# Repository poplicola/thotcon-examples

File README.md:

# Touch Wheel Badge - Demo Firmware Collection

This repository contains cleaned-up demo firmware for the touch wheel badge, suitable for public release and custom projects. Three different firmware examples are provided to showcase various capabilities of the hardware.

## Repository Contents

### 1. `tonechaser/` - Musical Tone Explorer
Advanced musical demonstration with multiple modes:
- **Free Play Mode**: Continuous tone generation based on touch position
- **Scale Mode**: Quantized musical scales
- **Chord Mode**: Play musical chords
- **Arpeggio Mode**: Automatic arpeggios
- **Visual Wheel**: Colorful wheel visualization with effects
- **Musical Features**: Multiple scales (Major, Minor, Pentatonic, Blues)

### 2. `working/` - Basic Touch Wheel Test
Simple touch wheel demonstration:
- **Touch Detection**: Basic capacitive touch wheel functionality
- **LED Indicators**: 6 LEDs that light up based on touch position
- **Calibration**: Automatic baseline calibration
- **Serial Output**: Debug data for development
- **Visual Feedback**: Simple wheel visualization on display

### 3. `wheel_visualization/` - Full Interactive Demo
Additional badge firmware with menu system:
- **Touch Wheel Demo**: Interactive capacitive touch wheel with visual feedback
- **Menu System**: Navigate between different modes using the touch wheel
- **Audio Feedback**: Simple tone feedback for interactions
- **Mini Games**: Placeholder for future game implementations
- **Credits Screen**: Information about the original creators
- **Clean Architecture**: Modular code structure for easy customization

## Hardware Requirements

All firmware examples work with the same hardware:

- **ESP32 microcontroller** (ESP32 Thing or compatible)
- **ST7789 TFT Display** (240x320 pixels)
- **6 LEDs** connected to GPIO pins
- **3 Capacitive touch sensors** for wheel input
- **Buzzer** for audio feedback
- **Center button** (capacitive touch)

## Pin Configuration

### TFT Display Pins
```cpp
#define TFT_MISO 19
#define TFT_MOSI 23
#define TFT_SCLK 18
#define TFT_CS   15  // Chip select control pin
#define TFT_DC    2  // Data Command control pin
#define TFT_RST   4  // Reset pin
```

### LED Pins
```cpp
#define LED_1_PIN 21
#define LED_2_PIN 22
#define LED_3_PIN 19
#define LED_4_PIN 17
#define LED_5_PIN 16
#define LED_6_PIN 25
```

### Touch Sensor Pins
```cpp
#define SELECT_PIN 27  // Center button
#define Q1_PIN 13      // Touch sensor 1
#define Q2_PIN 12      // Touch sensor 2
#define Q3_PIN 14      // Touch sensor 3
```

### Audio Pin
```cpp
#define BUZZER_PIN 5
```

## Getting Started

### 1. Install Arduino IDE
Download and install the [Arduino IDE](https://www.arduino.cc/en/software) if you haven't already.

### 2. Install ESP32 Board Package
1. In Arduino IDE, go to **File > Preferences**
2. Add this URL to "Additional Board Manager URLs":
   ```
   https://espressif.github.io/arduino-esp32/package_esp32_index.json
   ```
3. Go to **Tools > Board > Boards Manager**
4. Search for "esp32" and install the ESP32 package by Espressif

### 3. Install Required Libraries

#### TFT_eSPI Library
1. Go to **Sketch > Include Library > Manage Libraries**
2. Search for "TFT_eSPI" and install the library by Bodmer
3. **IMPORTANT**: You must configure the library for the ST7789 display

#### Configure TFT_eSPI for ST7789
1. Navigate to your Arduino libraries folder:
   - **Windows**: `Documents/Arduino/libraries/TFT_eSPI/`
   - **Mac**: `~/Documents/Arduino/libraries/TFT_eSPI/`
   - **Linux**: `~/Arduino/libraries/TFT_eSPI/`

2. Open `User_Setup.h` in a text editor

3. Comment out any existing driver and add these lines:
   ```cpp
   #define ST7789_DRIVER    // Configure for ST7789 display
   
   // Pin definitions (add these to User_Setup.h)
   #define TFT_MISO 19
   #define TFT_MOSI 23
   #define TFT_SCLK 18
   #define TFT_CS   15
   #define TFT_DC    2
   #define TFT_RST   4
   
   #define TFT_WIDTH  240
   #define TFT_HEIGHT 320
   ```

### 4. Choose and Upload Firmware
1. Choose one of the three firmware options:
   - `tonechaser/tonechaser.ino` - Musical demonstration
   - `working/working.ino` - Basic touch wheel test
   - `wheel_visualization/wheel_visualization.ino` - Full interactive demo
2. Open the chosen `.ino` file in Arduino IDE
3. Select your ESP32 board: **Tools > Board > ESP32 Arduino > ESP32 Thing** (or your specific ESP32 variant)
4. Select the correct COM port: **Tools > Port**
5. Click **Upload**

## Firmware Comparison

| Feature | working | tonechaser | wheel_visualization |
|---------|---------|------------|-------------------|
| Touch Detection | ✅ Basic | ✅ Advanced | ✅ Advanced |
| LED Control | ✅ | ✅ | ✅ |
| Audio Feedback | ❌ | ✅ Musical | ✅ Simple |
| Visual Display | ✅ Simple | ✅ Colorful | ✅ Interactive |
| Menu System | ❌ | ❌ | ✅ |
| Multiple Modes | ❌ | ✅ | ✅ |
| Calibration | ✅ | ✅ | ✅ |
| Serial Debug | ✅ | ❌ | ✅ |
| Code Complexity | Simple | Medium | Advanced |

## Usage

### Controls (All Firmware)
- **Touch Wheel**: Touch around the capacitive wheel to see visual feedback and light up LEDs
- **Center Button**: Press the center capacitive button (varies by firmware)
- **Calibration**: All firmware automatically calibrates on startup (don't touch during this phase)

### Specific Features by Firmware

#### `working/` - Basic Test
- Simple touch detection with LED feedback
- Displays raw sensor values and touch angle
- Best for hardware testing and development

#### `tonechaser/` - Musical Explorer
- Multiple musical modes (Free Play, Scale, Chord, Arpeggio)
- Press center button to cycle through modes
- Rich visual effects and musical scales
- Continuous tone generation based on touch position

#### `wheel_visualization/` - Interactive Demo
- Full menu system with navigation
- Touch wheel demo mode
- Placeholder mini-games section
- Credits screen
- Most complete user experience

## Customization

All firmware examples are designed to be easily modified:

- **Pin Configuration**: Modify pin definitions in each sketch
- **Touch Sensitivity**: Adjust touch thresholds
- **Colors and Effects**: Customize visual appearance
- **Audio**: Modify tones and musical scales
- **Menu Items**: Add new screens and functionality

## Troubleshooting

### Display Issues
- **Blank Screen**: Check TFT_eSPI configuration in `User_Setup.h`
- **Wrong Colors**: Verify `ST7789_DRIVER` is defined
- **Upside Down**: Adjust `tft.setRotation(0)` in setup()

### Touch Issues
- **No Touch Response**: Check capacitive touch sensor connections
- **Erratic Behavior**: May need recalibration or threshold adjustment
- **LEDs Not Working**: Verify LED pin connections

### Compilation Errors
- **Library Not Found**: Install TFT_eSPI library via Library Manager
- **Pin Conflicts**: Check pin definitions match your hardware setup
- **Memory Issues**: Try a simpler firmware if running out of memory

## Hardware Notes

This firmware was originally designed for a specific touch wheel badge but can be adapted for custom hardware. The touch wheel uses three capacitive sensors positioned 120° apart to triangulate touch position around a circular perimeter.

The algorithms calculate touch position using trigonometric interpolation between the three sensor readings, providing smooth and accurate position detection around the full 360° wheel.

## Development

Each firmware demonstrates different aspects of the hardware capabilities:

- **`working/`**: Foundation for understanding the basic touch detection algorithms
- **`tonechaser/`**: Advanced audio synthesis and visual effects
- **`wheel_visualization/`**: Complete UI framework and menu system

Use these as starting points for your own projects or as learning examples for capacitive touch wheel implementations.

## Credits

All credit to **Fourfold**. Visit [fourfold.co](https://fourfold.co) for more info.

## License

This is demonstration firmware provided as-is for educational and development purposes. WiFi functionality, splash screens, and proprietary content have been removed for public release.

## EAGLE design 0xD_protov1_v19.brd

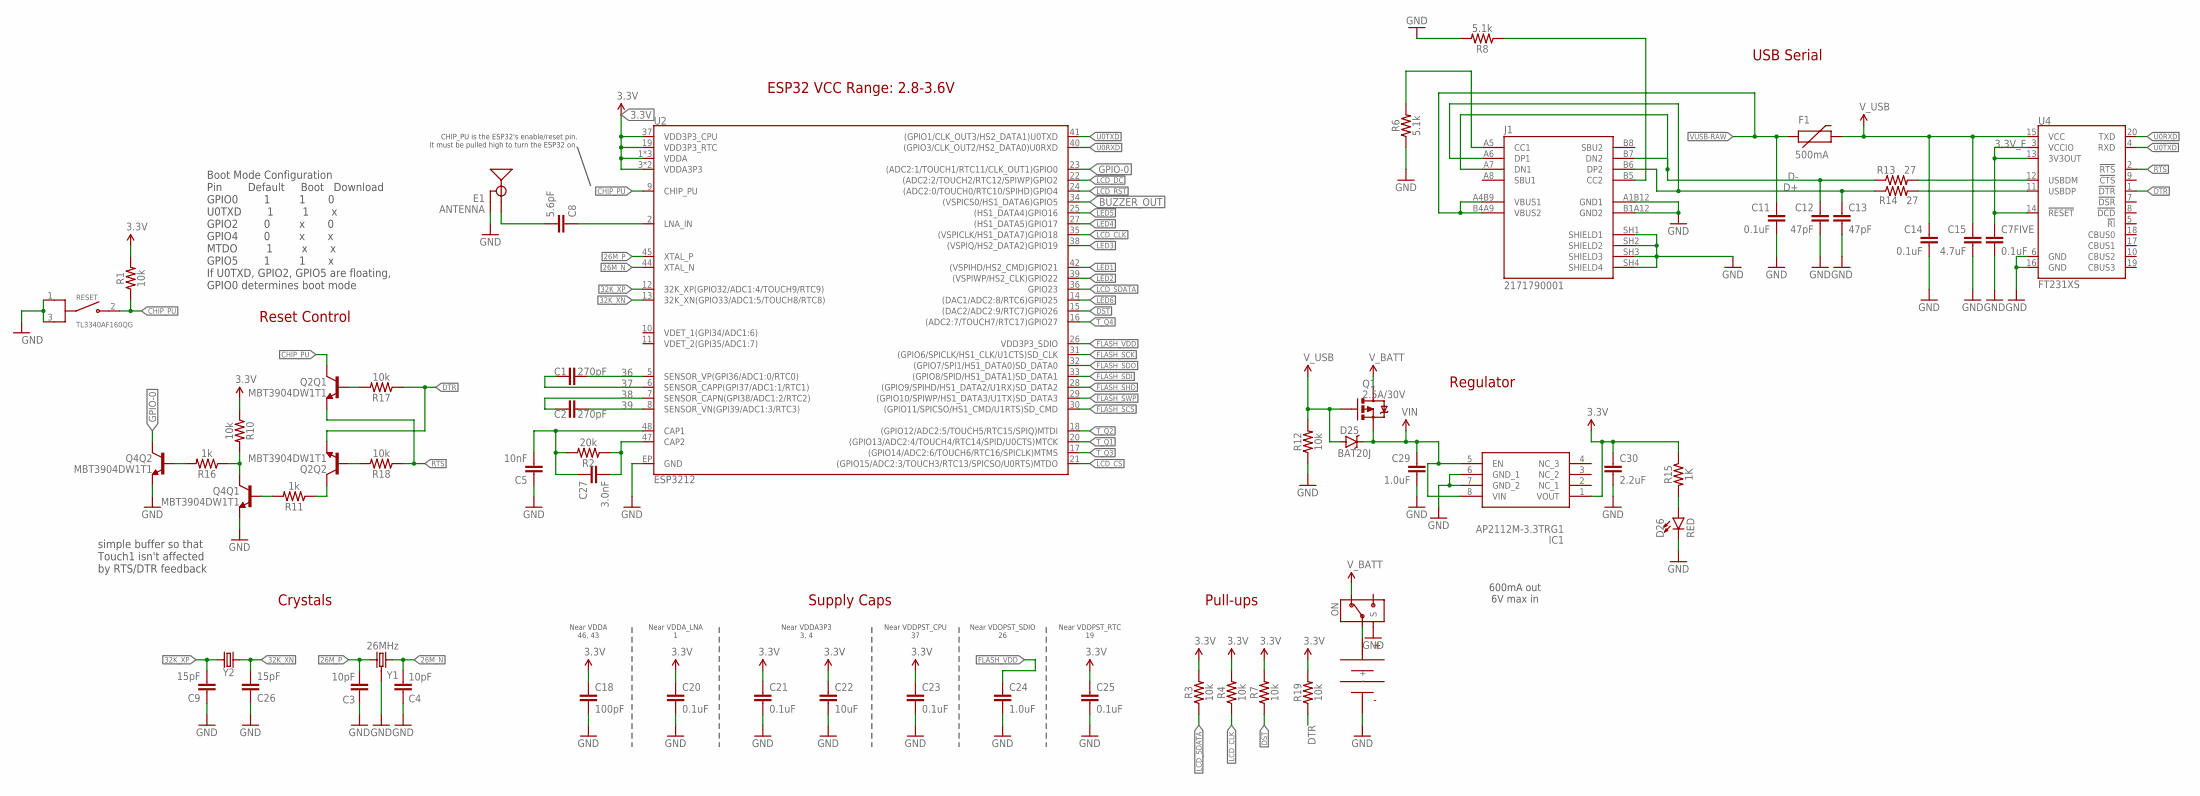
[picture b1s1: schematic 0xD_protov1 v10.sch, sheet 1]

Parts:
C1, C2: 270pF; 0603
C3, C4: 10pF; 0603
C5: 10nF; 0603
C7FIVE, C11, C14, C20, C21, C23, C25: 0.1uF; 0603
C8: 5.6pF; 0603
C9, C26: 15pF; 0603
C12, C13: 47pF; 0603
C15: 4.7uF; 0603
C18: 100pF; 0603
C22: 10uF; 0603
C24: 1.0uF; 0603
C27: 3.0nF; 0603
C29: 1.0uF; 0805
C30: 2.2uF; 0603
D25: BAT20J; SOD-323
D26: RED; LED-0603@1
E1: ANTENNA; TRACE_ANTENNA_2.4GHZ_25.7MM_TUNED
F1: 500mA; PTC-1206
G2: KEYSTONE_2479
IC1: AP2112M-3.3TRG1; SOIC127P600X170-8N
J1: 2171790001; MOLEX_2171790001
ON: CUS-12B; CUS-12_SPDT
Q1: 2.5A/30V; SOT23-3@1
Q2, Q4: MBT3904DW1T1; SC70-6
R1, R3, R4, R7, R10, R12, R17, R18, R19: 10k; 0603
R2: 20k; 0603
R6, R8: 5.1k; 0603
R11, R16: 1k; 0603
R13, R14: 27; 0603
R15: 1K; 0603
RESET: TL3340AF160QG; SW_TL3340AF160QG
U2: ESP3212; QFN48-0.4MM
U4: FT231XS; SSOP20_L
Y1: 26MHz; CRYSTAL-SMD-3.2X2.5
Y2: 32.768kHz; FC-12M

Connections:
3.3V: C18.1, C20.1, C21.1, C22.1, C23.1, C25.1, C30.1, IC1.1 (VOUT), R1.2, R3.2, R4.2, R7.2, R10.1, R15.1, R19.2, U2.1 (VDDA), U2.3 (VDDA3P3), U2.4 (VDDA3P3), U2.19 (VDD3P3_RTC), U2.37 (VDD3P3_CPU), U2.43 (VDDA), U2.46 (VDDA); also elsewhere on the board
3.3V_F: C7FIVE.1, U4.3 (VCCIO), U4.13 (3V3OUT), U4.14 (!RESET)
26M_N: C4.2, U2.44 (XTAL_N), Y1.3 (2)
26M_P: C3.2, U2.45 (XTAL_P), Y1.1
32K_XN: C26.2, U2.13 (32K_XN(GPIO33/ADC1:5/TOUCH8/RTC8)), Y2.2
32K_XP: C9.2, U2.12 (32K_XP(GPIO32/ADC1:4/TOUCH9/RTC9)), Y2.1
36: C1.2, U2.5 (SENSOR_VP(GPI36/ADC1:0/RTC0))
37: C1.1, U2.6 (SENSOR_CAPP(GPI37/ADC1:1/RTC1))
38: C2.1, U2.7 (SENSOR_CAPN(GPI38/ADC1:2/RTC2))
39: C2.2, U2.8 (SENSOR_VN(GPI39/ADC1:3/RTC3))
BUZZER_OUT: U2.34 ((VSPICS0/HS1_DATA6)GPIO5); also elsewhere on the board
CAP_10N: C5.2, C27.1, R2.2, U2.48 (CAP1)
CHIP_PU: Q2.3 (C), R1.1, RESET.2 (NO), U2.9 (CHIP_PU)
D+: C13.1, J1.A6 (DP1), J1.B6 (DP2), R14.1
D-: C12.1, J1.A7 (DN1), J1.B7 (DN2), R13.1
DST: R7.1, U2.15 ((DAC2/ADC2:9/RTC7)GPIO26)
DTR: Q2.1 (E), R17.1, R19.1, U4.1 (!DTR)
FLASH_SCK: U2.31 ((GPIO6/SPICLK/HS1_CLK/U1CTS)SD_CLK); also elsewhere on the board
FLASH_SCS: U2.30 ((GPIO11/SPICSO/HS1_CMD/U1RTS)SD_CMD); also elsewhere on the board
FLASH_SDI: U2.33 ((GPIO8/SPID/HS1_DATA1)SD_DATA1); also elsewhere on the board
FLASH_SDO: U2.32 ((GPIO7/SPI1/HS1_DATA0)SD_DATA0); also elsewhere on the board
FLASH_SHD: U2.28 ((GPIO9/SPIHD/HS1_DATA2/U1RX)SD_DATA2); also elsewhere on the board
FLASH_SWP: U2.29 ((GPIO10/SPIWP/HS1_DATA3/U1TX)SD_DATA3); also elsewhere on the board
FLASH_VDD: C24.1, U2.26 (VDD3P3_SDIO); also elsewhere on the board
GND: C3.1, C4.1, C5.1, C7FIVE.2, C9.1, C11.2, C12.2, C13.2, C14.2, C15.2, C18.2, C20.2, C21.2, C22.2, C23.2, C24.2, C25.2, C26.1, C29.2, C30.2, D26.C, E1.GND, E1.GND2 (GND), G2.-, IC1.6 (GND_1), IC1.7 (GND_2), J1.A1B12 (GND1), J1.B1A12 (GND2), J1.SH1 (SHIELD1), J1.SH2 (SHIELD2), J1.SH3 (SHIELD3), J1.SH4 (SHIELD4), ON.P$4 (S), ON.P$5 (S), ON.P$6 (S), ON.P$7 (S), Q4.1 (E), Q4.4 (E), R6.1, R8.2, R12.1, RESET.1 (COM_1), RESET.3 (COM_2), U2.EP (GND), U4.6 (GND), U4.16 (GND), Y1.2 (GND), Y1.4 (GND); also elsewhere on the board
GPIO-0: Q4.6 (C), U2.23 ((ADC2:1/TOUCH1/RTC11/CLK_OUT1)GPIO0)
LCD_CLK: R4.1, U2.35 ((VSPICLK/HS1_DATA7)GPIO18); also elsewhere on the board
LCD_CS: U2.21 ((GPIO15/ADC2:3/TOUCH3/RTC13/SPICSO/U0RT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); also elsewhere on the board
LCD_DC: U2.22 ((ADC2:2/TOUCH2/RTC12/SPIWP)GPIO2); also elsewhere on the board
LCD_RST: U2.24 ((ADC2:0/TOUCH0/RTC10/SPIHD)GPIO4); also elsewhere on the board
LCD_SDATA: R3.1, U2.36 (GPIO23); also elsewhere on the board
LED1: U2.42 ((VSPIHD/HS2_CMD)GPIO21); also elsewhere on the board
LED2: U2.39 ((VSPIWP/HS2_CLK)GPIO22); also elsewhere on the board
LED3: U2.38 ((VSPIQ/HS2_DATA2)GPIO19); also elsewhere on the board
LED4: U2.27 ((HS1_DATA5)GPIO17); also elsewhere on the board
LED5: U2.25 ((HS1_DATA4)GPIO16); also elsewhere on the board
LED6: U2.14 ((DAC1/ADC2:8/RTC6)GPIO25); also elsewhere on the board
LNA_IN: C8.1, U2.2 (LNA_IN)
unnamed: C27.2, R2.1, U2.47 (CAP2)
unnamed: J1.A5 (CC1), R6.2
unnamed: R13.2, U4.12 (USBDM)
unnamed: R14.2, U4.11 (USBDP)
unnamed: Q4.2 (B), R16.2
unnamed: Q2.5 (B), R17.2
unnamed: J1.B5 (CC2), R8.1
unnamed: Q2.2 (B), R18.2
unnamed: Q4.3 (C), R10.2, R16.1
unnamed: Q4.5 (B), R11.2
unnamed: Q2.6 (C), R11.1
unnamed: G2.+, ON.P$2 (1)
unnamed: D26.A, R15.2
RTS: Q2.4 (E), R18.1, U4.2 (!RTS)
TRACE_ANT: C8.2, E1.ANT (SIGNAL)
T_Q1: U2.20 ((GPIO13/ADC2:4/TOUCH4/RTC14/SPID/U0CTS)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)
T_Q2: U2.18 ((GPIO12/ADC2:5/TOUCH5/RTC15/SPIQ)MTDI)
T_Q3: U2.17 ((GPIO14/ADC2:6/TOUCH6/RTC16/SPICLK)MTMS)
T_Q4: U2.16 ((ADC2:7/TOUCH7/RTC17)GPIO27); also elsewhere on the board
U0RXD: U2.40 ((GPIO3/CLK_OUT2/HS2_DATA0)U0RXD), U4.20 (TXD)
U0TXD: U2.41 ((GPIO1/CLK_OUT3/HS2_DATA1)U0TXD), U4.4 (RXD)
VIN: C29.1, D25.C, IC1.5 (EN), IC1.8 (VIN), Q1.2 (S)
VUSB-RAW: C11.1, F1.1, J1.A4B9 (VBUS1), J1.B4A9 (VBUS2)
V_BATT: ON.P$1 (2), Q1.3 (D)
V_USB: C14.1, C15.1, D25.A, F1.2, Q1.1 (G), R12.2, U4.15 (VCC)

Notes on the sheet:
Near VDDA 46, 43
Near VDDA_LNA 1
Near VDDA3P3 3, 4
Near VDDPST_CPU 37
Near VDDPST_SDIO 26
Near VDDPST_RTC 19
ESP32 VCC Range: 2.8-3.6V
CHIP_PU is the ESP32's enable/reset pin. It must be pulled high to turn the ESP32 on.
Supply Caps
Reset Control
Crystals
600mA out 6V max in
Regulator
USB Serial
Boot Mode Configuration Pin Default Boot Download GPIO0 1 1 0 U0TXD 1 1 x GPIO2 0 x 0 GPIO4 0 x x MTDO 1 x x GPIO5 1 1 x If U0TXD, GPIO2, GPIO5 are floating, GPIO0 determines boot mode
Pull-ups
simple buffer so that Touch1 isn't affected by RTS/DTR feedback

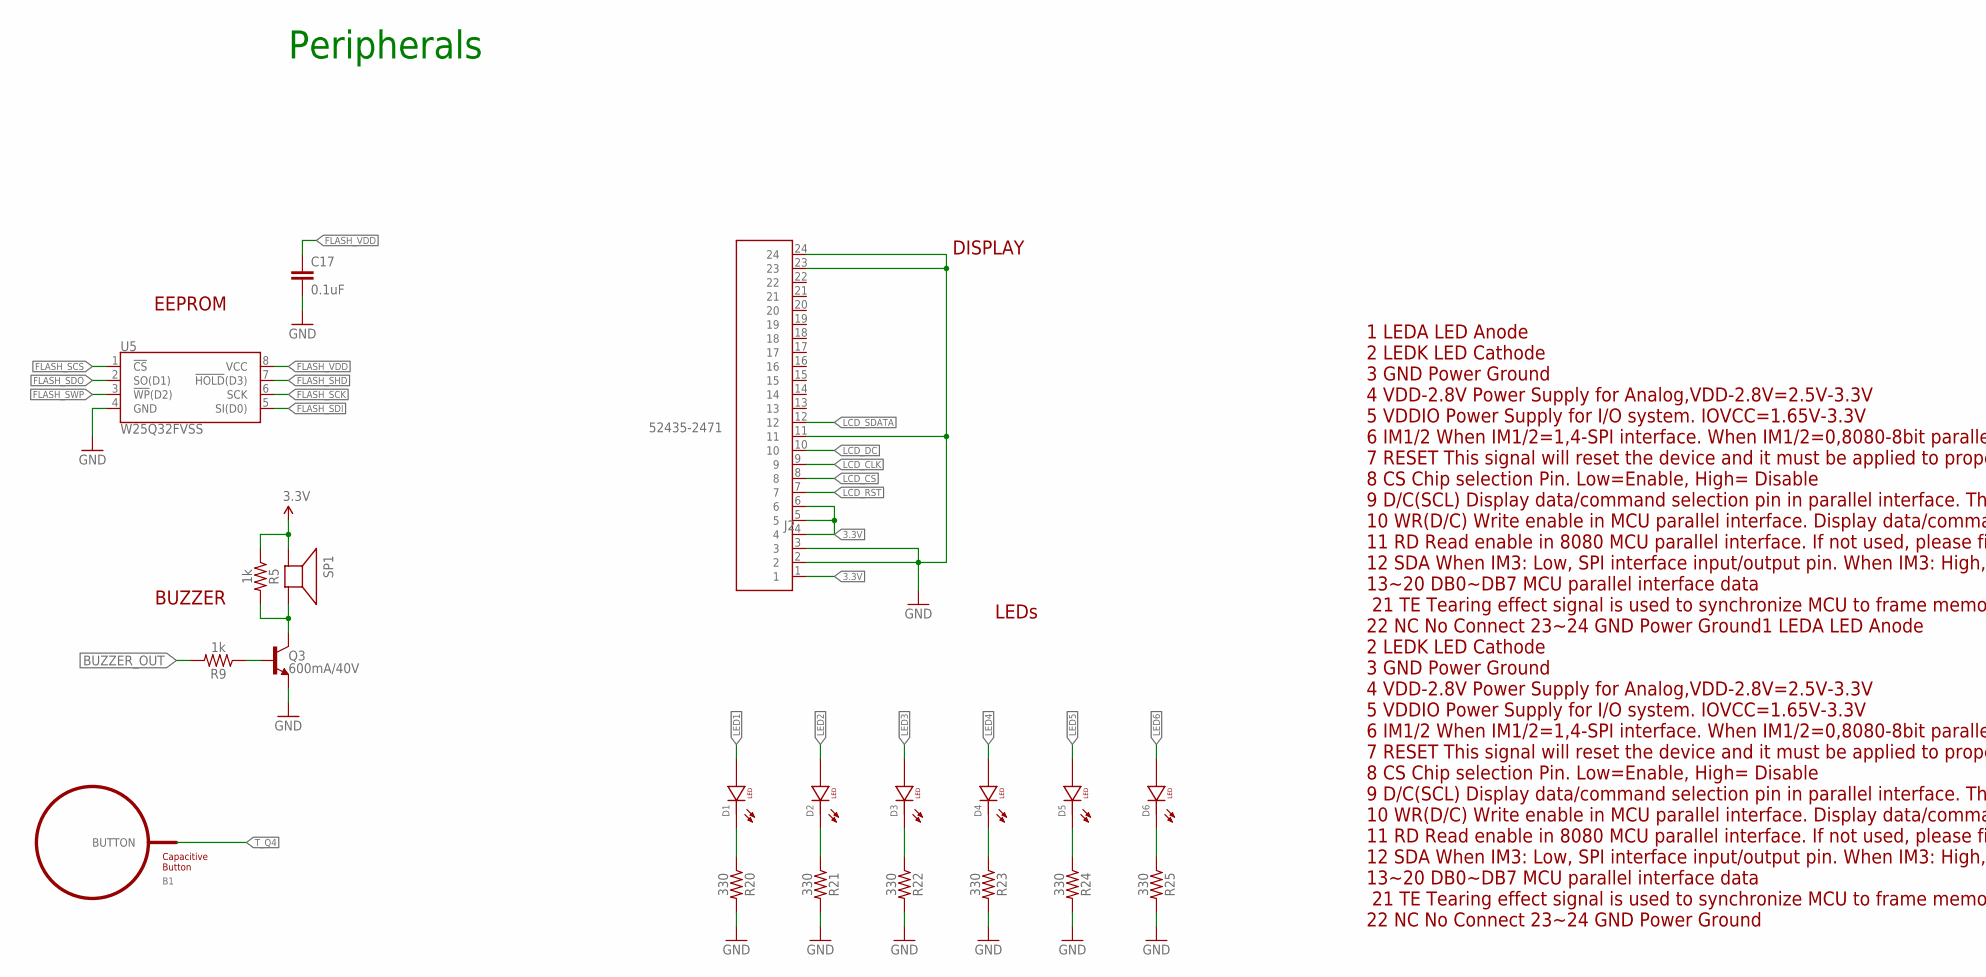
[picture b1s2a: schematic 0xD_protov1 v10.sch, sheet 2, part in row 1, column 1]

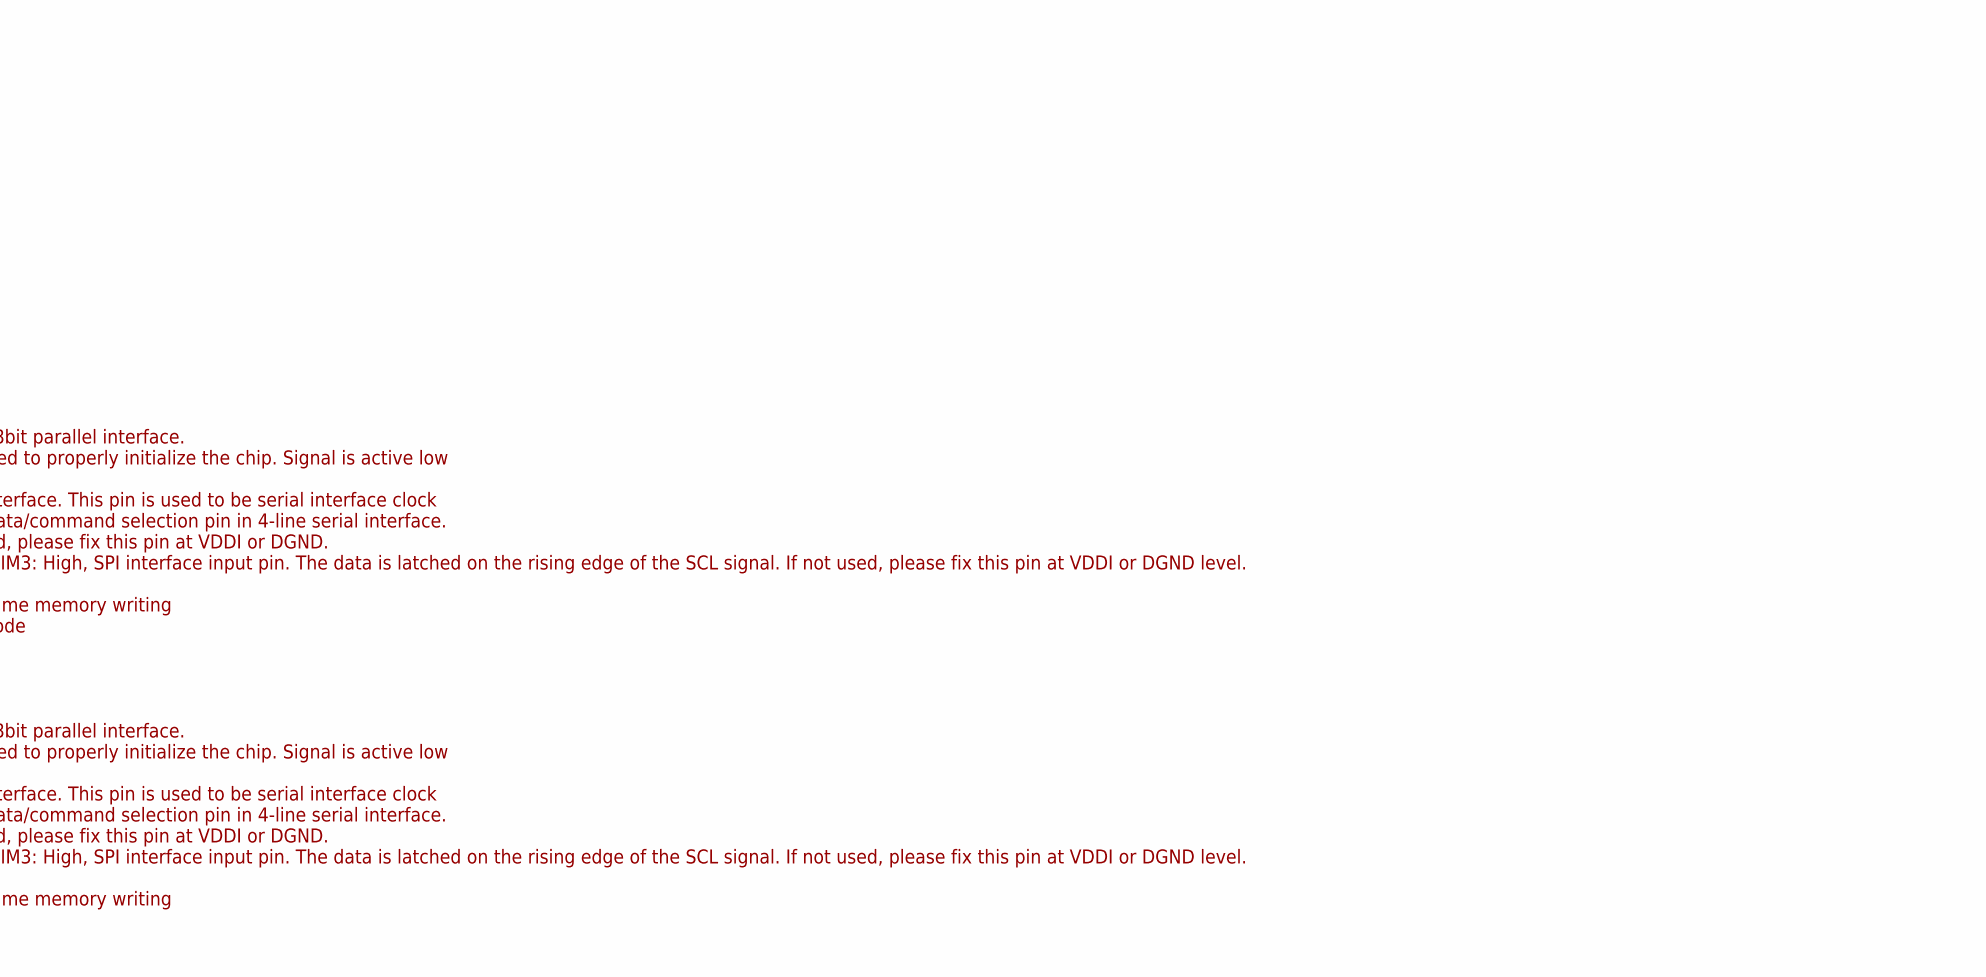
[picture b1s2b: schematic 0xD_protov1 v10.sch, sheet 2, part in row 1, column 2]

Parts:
B1: BUTTON_PASSIVE12MM; BUTTON_PASSIVE_12MM
C17: 0.1uF; 0603
D1, D2, D3, D4, D5, D6: XZDGK45WT-9-GREEN-REV; XZ-PLCC2-REV-HOLE
J2: 52435-2471; MOLEX_52435-2471
Q3: 600mA/40V; SOT23-3
R5, R9: 1k; 0603
R20, R21, R22, R23, R24, R25: 330; 0603
SP1: SPEAKER/PS12; PS12
U5: W25Q32FVSS; SOIC-8

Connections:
3.3V: J2.1, J2.4, J2.5, J2.6, R5.1, SP1.P$1 (+); also elsewhere on the board
BUZZER_OUT: R9.2; also elsewhere on the board
FLASH_SCK: U5.6 (SCK); also elsewhere on the board
FLASH_SCS: U5.1 (!CS!); also elsewhere on the board
FLASH_SDI: U5.5 (SI(D0)); also elsewhere on the board
FLASH_SDO: U5.2 (SO(D1)); also elsewhere on the board
FLASH_SHD: U5.7 (!HOLD!(D3)); also elsewhere on the board
FLASH_SWP: U5.3 (!WP!(D2)); also elsewhere on the board
FLASH_VDD: C17.1, U5.8 (VCC); also elsewhere on the board
GND: C17.2, J2.2, J2.3, J2.11, J2.23, J2.24, Q3.2 (E), R20.2, R21.2, R22.2, R23.2, R24.2, R25.2, U5.4 (GND); also elsewhere on the board
LCD_CLK: J2.9; also elsewhere on the board
LCD_CS: J2.8; also elsewhere on the board
LCD_DC: J2.10; also elsewhere on the board
LCD_RST: J2.7; also elsewhere on the board
LCD_SDATA: J2.12; also elsewhere on the board
LED1: D1.ANODE; also elsewhere on the board
LED2: D2.ANODE; also elsewhere on the board
LED3: D3.ANODE; also elsewhere on the board
LED4: D4.ANODE; also elsewhere on the board
LED5: D5.ANODE; also elsewhere on the board
LED6: D6.ANODE; also elsewhere on the board
unnamed: D1.CATHODE, R20.1
unnamed: D2.CATHODE, R21.1
unnamed: Q3.3 (C), R5.2, SP1.P$2 (-)
unnamed: D3.CATHODE, R22.1
unnamed: D4.CATHODE, R23.1
unnamed: D5.CATHODE, R24.1
unnamed: D6.CATHODE, R25.1
unnamed: Q3.1 (B), R9.1
T_Q4: B1.BUTTON; also elsewhere on the board

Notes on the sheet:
EEPROM
BUZZER
Peripherals
DISPLAY
LEDs
1 LEDA LED Anode 2 LEDK LED Cathode 3 GND Power Ground 4 VDD-2.8V Power Supply for Analog,VDD-2.8V=2.5V-3.3V 5 VDDIO Power Supply for I/O system. IOVCC=1.65V-3.3V 6 IM1/2 When IM1/2=1,4-SPI interface. When IM1/2=0,8080-8bit parallel interface. 7 RESET This signal will reset the device and it must b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

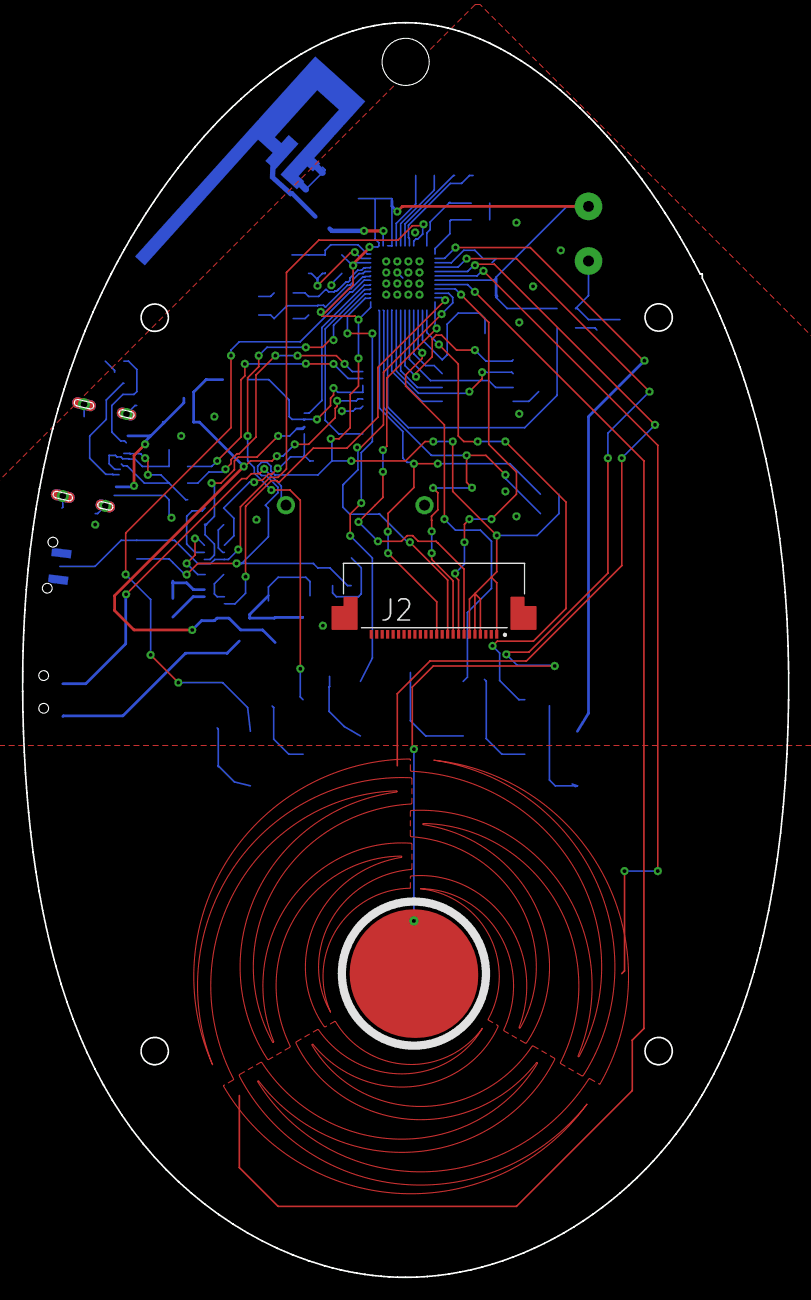
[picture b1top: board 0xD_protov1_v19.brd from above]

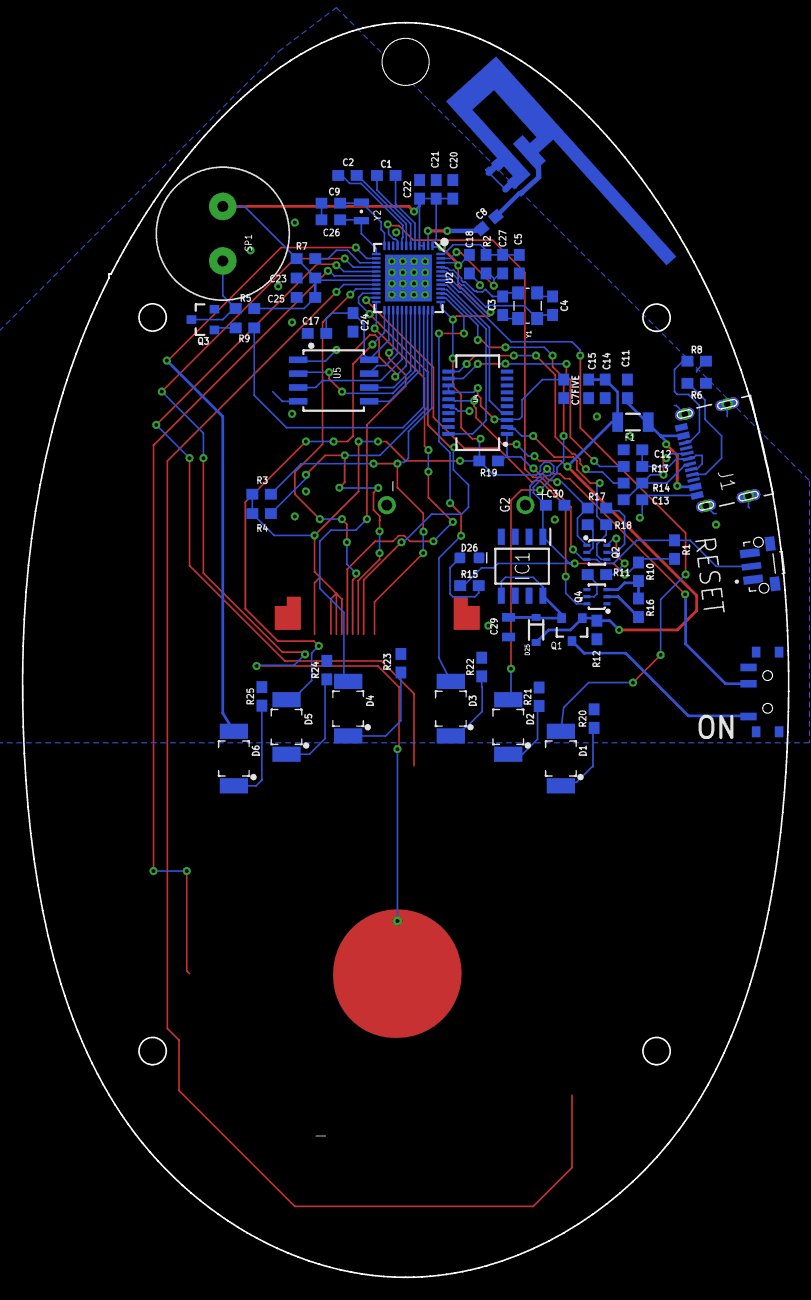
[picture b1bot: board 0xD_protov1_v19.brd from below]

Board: 2 copper layers, 70.2 x 115.0 mm, 77 parts (75 on the bottom side), 68 nets.

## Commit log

2025-06-18 Add board files
2025-06-20 Remove DS Store
2025-06-20 Smash more hidden dirs

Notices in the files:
parts and their libraries:
SparkFun-Aesthetics: Licensing: Creative Commons ShareAlike 4.0 International - https://creativecommons.org/licenses/by-sa/4.0
SparkFun-DigitalIC: Licensing: CC v3.0 Share-Alike You are welcome to use this library for commercial purposes.
